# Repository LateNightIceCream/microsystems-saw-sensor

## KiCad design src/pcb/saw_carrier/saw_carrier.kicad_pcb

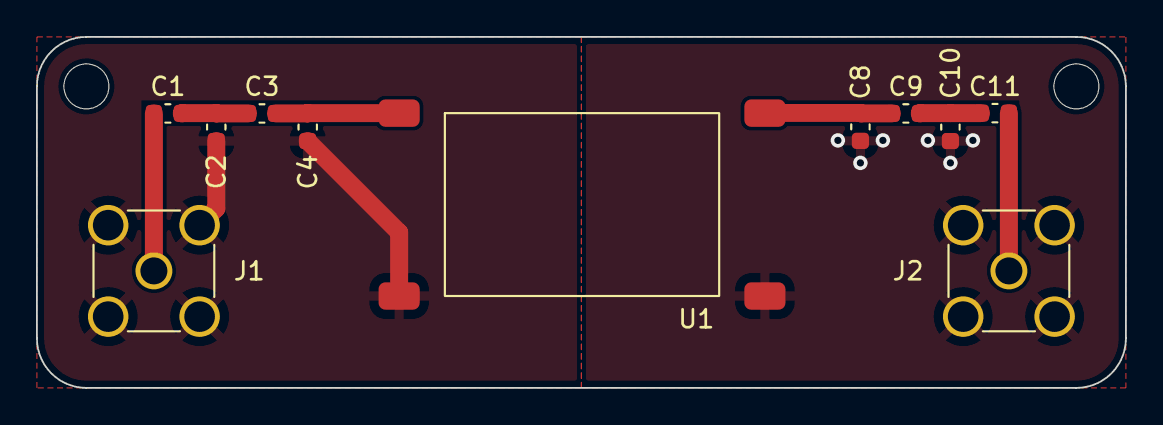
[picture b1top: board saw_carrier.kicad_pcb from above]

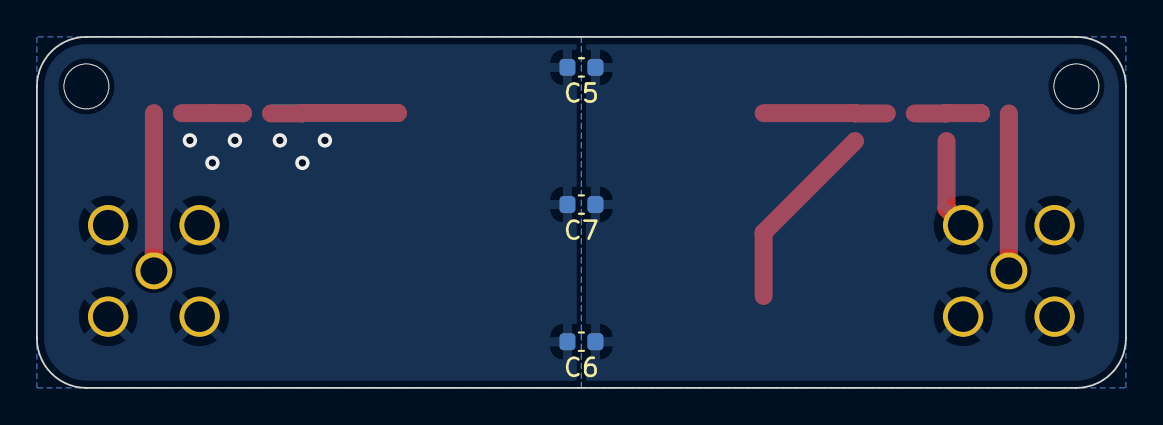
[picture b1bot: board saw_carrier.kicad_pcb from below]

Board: 2 copper layers, 60.5 x 19.5 mm, 16 parts (3 on the bottom side), 8 nets.

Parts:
C1, C2, C3, C4, C5, C6, C7, C8, C9, C10, C11: C_Small; C_0603_1608Metric
H1, H3: MountingHole; MountingHole_2.5mm
J1, J2: Conn_Coaxial; SMA_Amphenol_132134-11_Vertical
U1: SAW_Sensor; saw_sensor

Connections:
/IN_0: C3.2, C4.2, U1.1 (IN)
/IN_1: C1.2, C2.2, C3.1
/IN_2: C1.1, J1.1 (In)
/OUT_0: C8.2, C9.1, U1.3 (OUT)
/OUT_1: C9.2, C10.2, C11.1
/OUT_2: C11.2, J2.1 (In)
GND1: C2.1, C4.1, C5.1, C6.1, C7.1, J1.2 (Ext), U1.2 (GND1)
GND2: C5.2, C6.2, C7.2, C8.1, C10.1, J2.2 (Ext), U1.4 (GND2)

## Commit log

2023-04-20 init document
2023-04-20 nix build test
2023-05-25 init pcb
2023-05-25 rename pcb project folder
2023-06-13 Add files via upload
    Aufnahmen und Analysen aus dem Mikroskop
2023-06-20 rename folder for pics
2023-06-20 remove obsolete folder
